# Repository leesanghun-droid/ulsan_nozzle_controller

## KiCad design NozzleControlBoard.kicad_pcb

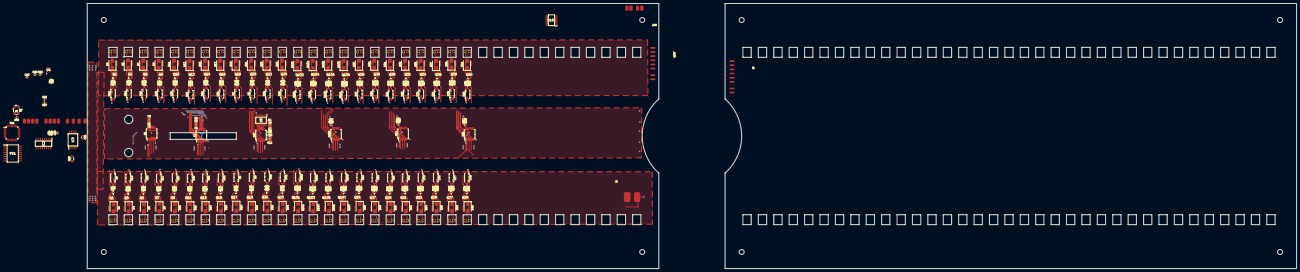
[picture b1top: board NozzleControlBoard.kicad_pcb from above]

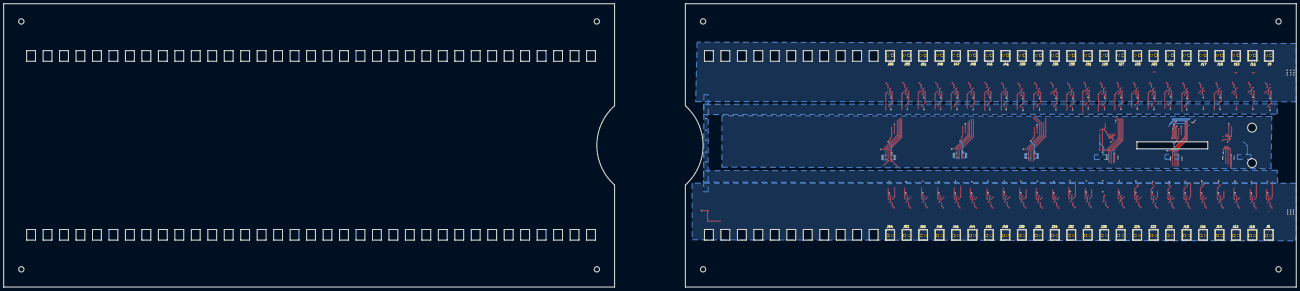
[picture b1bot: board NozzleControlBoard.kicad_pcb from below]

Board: 4 copper layers, 345.0 x 160.0 mm, 391 parts (48 on the bottom side), 276 nets.

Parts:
C1, C4, C7, C10, C16, C21, C24, C65: 0.1uF; C_0603_1608Metric
C2, C5, C8, C11, C17, C22, C25, C41, C66: 1uF; C_0603_1608Metric
C3, C6, C9, C12, C19, C23, C26, C51, C67: 10uF; C_0603_1608Metric
C18: 100uF; C_1206_3216Metric
C20, C46: NC; C_0603_1608Metric
C55: NC; C_0805_2012Metric
C63, C64: 10pF; C_0603_1608Metric
D1, D3, D4, D5, D6, D7, D8, D9, D10, D11, D12, D13, D14, D15, D16, D17, D18, D19, D20, D21, D22, D23, D24, D25, D26, D27, D28, D29, D30, D31, D32, D33, D34, D35, D36, D37, D38, D39, D40, D41, D101, D102, D103, D104, D105, D106, D107, D108: DIODE; D_SMB
IC2: MAX3094EESE+; SOIC127P600X175-16N
IC3: MAX22245BAWA+; SOIC127P1031X265-8N
J1: 24V_OUT; 24V_PAD
J2, J103: SHIFT_DATA_TOSS
J3: Conn_01x12_Male; input_pad
J8: SOL1; 2PIN
J9: SOL2; 2PIN
J10: SOL3; 2PIN
J11: SOL4; 2PIN
J12: SOL5; 2PIN
J13: SOL6; 2PIN
J14: SOL7; 2PIN
J15: SOL8; 2PIN
J16: SOL9; 2PIN
J17: SOL10; 2PIN
J18: SOL11; 2PIN
J19: SOL12; 2PIN
J20: SOL13; 2PIN
J21: SOL14; 2PIN
J22: SOL15; 2PIN
J23: SOL16; 2PIN
J24: SOL17; 2PIN
J25: SOL18; 2PIN
J26: SOL19; 2PIN
J27: SOL20; 2PIN
J28: SOL21; 2PIN
J29: SOL22; 2PIN
J30: SOL23; 2PIN
J31: SOL24; 2PIN
J32: SOL25; 2PIN
J33: SOL26; 2PIN
J34: SOL27; 2PIN
J35: SOL28; 2PIN
J36: SOL29; 2PIN
J37: SOL30; 2PIN
J38: SOL31; 2PIN
J39: SOL32; 2PIN
J40: SOL33; 2PIN
J41: SOL34; 2PIN
J42: SOL35; 2PIN
J43: SOL36; 2PIN
J44: SOL37; 2PIN
J45: SOL38; 2PIN
J46: SOL39; 2PIN
J47: SOL40; 2PIN
J48: SOL41; 2PIN
J49: SOL42; 2PIN
J50: SOL43; 2PIN
J51: SOL44; 2PIN
J52: SOL45; 2PIN
J53: SOL46; 2PIN
J54: SOL47; 2PIN
J55: SOL48; 2PIN
PS1: R05CTE05S-R; SOIC127P1030X265-16N
Q1, Q2, Q3, Q4, Q5, Q6, Q7, Q8, Q9, Q10, Q11, Q12, Q13, Q14, Q15, Q16, Q17, Q18, Q19, Q20, Q21, Q22, Q23, Q24, Q25, Q26, Q27, Q28, Q29, Q30, Q31, Q32, Q33, Q34, Q35, Q36, Q37, Q38, Q39, Q40, Q101, Q102, Q103, Q104, Q105, Q106, Q107, Q108: TPN22006NH,LQ; TPN22006NHLQ
R1: 100Ω; R_0603_1608Metric
R2, R3, R4, R5, R6, R7, R8, R9, R21, R22, R23, R24, R26, R27, R28, R29, R54, R56, R57, R58, R59, R61, R62, R63, R106, R107, R108, R109, R110, R111, R112, R113, R138, R139, R140, R141, R142, R143, R144, R145, R170, R171, R172, R173, R174, R175, R176, R177: 3.3kΩ; R_0603_1608Metric
R10, R11, R12, R13, R14, R15, R16, R17, R18, R19, R20, R25, R30, R31, R32, R33, R34, R35, R36, R37, R38, R39, R40, R41, R42, R43, R47, R48, R49, R50, R51, R64, R65, R66, R67, R68, R69, R70, R71, R72, R73, R74, R75, R76, R77, R78, R79, R96, R114, R115, R116, R117, R118, R119, R120, R121, R122, R123, R124, R125, R126, R127, R128, R129, R146, R147, R148, R149, R150, R151, R152, R153, R154, R155, R156, R157, R158, R159, R160, R161, R178, R179, R180, R181, R182, R183, R184, R185, R186, R187, R188, R189, R190, R191, R192, R193: 22kΩ; R_0603_1608Metric
R52: 5kΩ; R_0603_1608Metric
R55: 2kΩ; R_0603_1608Metric
R60: NC; R_0603_1608Metric
U1, U2, U47, U64, U81, U102: 74HCT595; SSOP-16_5.3x6.2mm_P0.65mm
U3, U6, U7, U8, U9, U12, U13, U14, U15, U16, U17, U18, U27, U28, U29, U30, U31, U32, U33, U34, U43, U44, U45, U46, U56, U57, U58, U59, U60, U61, U62, U63, U73, U74, U75, U76, U77, U78, U79, U80, U103, U104, U105, U106, U107, U108, U109, U110: TLP291; SOIC-4_4.55x2.6mm_P1.27mm
U4: ISP; TPN22006NHLQ
U5, U101: 74HC244; SOP65P640X110-20N
U11: ATmega8A-A; TQFP-32_7x7mm_P0.8mm
U87: SOL14; sol_pad
Y1: Crystal_GND24; Crystal_SMD_Abracon_ABM3B-4Pin_5.0x3.2mm

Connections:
/3.3V_3: IC2.4 (ENAC), IC2.12 (ENBD), IC2.16 (VCC), IC3.1 (VDDA)
/5V_3: C18.2, C20.2, C41.2, C46.2, C51.1, C55.1, J2.8, J3.1, J103.8, PS1.3 (+VIN_1), PS1.4 (+VIN_2)
/5V_4: C1.2, C2.2, C3.1, C4.2, C5.2, C6.1, C7.2, C8.2, C9.1, C10.2, C11.2, C12.1, C16.2, C17.2, C19.1, C21.2, C22.2, C23.1, C24.2, C25.2, C26.1, C65.2, C66.2, C67.1, IC3.8 (VDDB), J2.5, J103.5, PS1.13 (+VOUT_1), PS1.14 (+VOUT_2), R52.2, R55.1, R60.1, U1.10 (~SRCLR), U1.16 (VCC), U2.10 (~SRCLR), U2.16 (VCC), U3.1, U5.20 (VCC), U6.1, U7.1, U8.1, U9.1, U11.4 (VCC), U11.6 (VCC), U12.1, U13.1, U14.1, U15.1, U16.1, U17.1, U18.1, U27.1, U28.1, U29.1, U30.1, U31.1, U32.1, U33.1, U34.1, U43.1, U44.1, U45.1, U46.1, U47.10 (~SRCLR), U47.16 (VCC), U56.1, U57.1, U58.1, U59.1, U60.1, U61.1, U62.1, U63.1, U64.10 (~SRCLR), U64.16 (VCC), U73.1, U74.1, U75.1, U76.1, U77.1, U78.1, U79.1, U80.1, U81.10 (~SRCLR), U81.16 (VCC), U101.20 (VCC), U102.10 (~SRCLR), U102.16 (VCC), U103.1, U104.1, U105.1, U106.1, U107.1, U108.1, U109.1, U110.1
/24V2: J1.2, J3.9, J3.10, J3.11, J3.12, J8.1, J9.1, J10.1, J11.1, J12.1, J13.1, J14.1, J15.1, J16.1, J17.1, J18.1, J19.1, J20.1, J21.1, J22.1, J23.1, J24.1, J25.1, J26.1, J27.1, J28.1, J29.1, J30.1, J31.1, J32.1, J33.1, J34.1, J35.1, J36.1, J37.1, J38.1, J39.1, J40.1, J41.1, J42.1, J43.1, J44.1, J45.1, J46.1, J47.1, J48.1, J49.1, J50.1, J51.1, J52.1, J53.1, J54.1, J55.1, U3.4, U6.4, U7.4, U8.4, U9.4, U12.4, U13.4, U14.4, U15.4, U16.4, U17.4, U18.4, U27.4, U28.4, U29.4, U30.4, U31.4, U32.4, U33.4, U34.4, U43.4, U44.4, U45.4, U46.4, U56.4, U57.4, U58.4, U59.4, U60.4, U61.4, U62.4, U63.4, U73.4, U74.4, U75.4, U76.4, U77.4, U78.4, U79.4, U80.4, U87.1 (SOL+), U103.4, U104.4, U105.4, U106.4, U107.4, U108.4, U109.4, U110.4
/24V2_GND: D1.1 (K), D3.1 (K), D4.1 (K), D5.1 (K), D6.1 (K), D7.1 (K), D8.1 (K), D9.1 (K), D10.1 (K), D11.1 (K), D12.1 (K), D13.1 (K), D14.1 (K), D15.1 (K), D16.1 (K), D17.1 (K), D18.1 (K), D19.1 (K), D20.1 (K), D21.1 (K), D22.1 (K), D23.1 (K), D24.1 (K), D25.1 (K), D26.1 (K), D27.1 (K), D28.1 (K), D29.1 (K), D30.1 (K), D31.1 (K), D32.1 (K), D33.1 (K), D34.1 (K), D35.1 (K), D36.1 (K), D37.1 (K), D38.1 (K), D39.1 (K), D40.1 (K), D41.1 (K), D101.1 (K), D102.1 (K), D103.1 (K), D104.1 (K), D105.1 (K), D106.1 (K), D107.1 (K), D108.1 (K), J1.1, J3.5, J3.6, J3.7, J3.8, Q1.1 (S_1), Q1.2 (S_2), Q1.3 (S_3), Q2.1 (S_1), Q2.2 (S_2), Q2.3 (S_3), Q3.1 (S_1), Q3.2 (S_2), Q3.3 (S_3), Q4.1 (S_1), Q4.2 (S_2), Q4.3 (S_3), Q5.1 (S_1), Q5.2 (S_2), Q5.3 (S_3), Q6.1 (S_1), Q6.2 (S_2), Q6.3 (S_3), Q7.1 (S_1), Q7.2 (S_2), Q7.3 (S_3), Q8.1 (S_1), Q8.2 (S_2), Q8.3 (S_3), Q9.1 (S_1), Q9.2 (S_2), Q9.3 (S_3), Q10.1 (S_1), Q10.2 (S_2), Q10.3 (S_3), Q11.1 (S_1), Q11.2 (S_2), Q11.3 (S_3), Q12.1 (S_1), Q12.2 (S_2), Q12.3 (S_3), Q13.1 (S_1), Q13.2 (S_2), Q13.3 (S_3), Q14.1 (S_1), Q14.2 (S_2), Q14.3 (S_3), Q15.1 (S_1), Q15.2 (S_2), Q15.3 (S_3), Q16.1 (S_1), Q16.2 (S_2), Q16.3 (S_3), Q17.1 (S_1), Q17.2 (S_2), Q17.3 (S_3), Q18.1 (S_1), Q18.2 (S_2), Q18.3 (S_3), Q19.1 (S_1), Q19.2 (S_2), Q19.3 (S_3), Q20.1 (S_1), Q20.2 (S_2), Q20.3 (S_3), Q21.1 (S_1), Q21.2 (S_2), Q21.3 (S_3), Q22.1 (S_1), Q22.2 (S_2), Q22.3 (S_3), Q23.1 (S_1), Q23.2 (S_2), Q23.3 (S_3), Q24.1 (S_1), Q24.2 (S_2), Q24.3 (S_3), Q25.1 (S_1), Q25.2 (S_2), Q25.3 (S_3), Q26.1 (S_1), Q26.2 (S_2), Q26.3 (S_3), Q27.1 (S_1), Q27.2 (S_2), Q27.3 (S_3), Q28.1 (S_1), Q28.2 (S_2), Q28.3 (S_3), Q29.1 (S_1), Q29.2 (S_2), Q29.3 (S_3), Q30.1 (S_1), Q30.2 (S_2), Q30.3 (S_3), Q31.1 (S_1), Q31.2 (S_2), Q31.3 (S_3), Q32.1 (S_1), Q32.2 (S_2), Q32.3 (S_3), Q33.1 (S_1), Q33.2 (S_2), Q33.3 (S_3), Q34.1 (S_1), Q34.2 (S_2), Q34.3 (S_3), Q35.1 (S_1), Q35.2 (S_2), Q35.3 (S_3), Q36.1 (S_1), Q36.2 (S_2), Q36.3 (S_3), Q37.1 (S_1), Q37.2 (S_2), Q37.3 (S_3), Q38.1 (S_1), Q38.2 (S_2), Q38.3 (S_3), Q39.1 (S_1), Q39.2 (S_2), Q39.3 (S_3), Q40.1 (S_1), Q40.2 (S_2), Q40.3 (S_3), Q101.1 (S_1), Q101.2 (S_2), Q101.3 (S_3), Q102.1 (S_1), Q102.2 (S_2), Q102.3 (S_3), Q103.1 (S_1), Q103.2 (S_2), Q103.3 (S_3), Q104.1 (S_1), Q104.2 (S_2), Q104.3 (S_3), Q105.1 (S_1), Q105.2 (S_2), Q105.3 (S_3), Q106.1 (S_1), Q106.2 (S_2), Q106.3 (S_3), Q107.1 (S_1), Q107.2 (S_2), Q107.3 (S_3), Q108.1 (S_1), Q108.2 (S_2), Q108.3 (S_3), R11.2, R13.2, R15.2, R17.2, R19.2, R25.2, R31.2, R34.2, R36.2, R38.2, R40.2, R43.2, R47.2, R49.2, R51.2, R65.2, R67.2, R69.2, R71.2, R73.2, R75.2, R77.2, R79.2, R96.2, R115.2, R117.2, R119.2, R121.2, R123.2, R125.2, R127.2, R129.2, R147.2, R149.2, R151.2, R153.2, R155.2, R157.2, R159.2, R161.2, R179.2, R181.2, R183.2, R185.2, R187.2, R189.2, R191.2, R193.2
/CLK: J2.4, U1.11 (SRCLK), U2.11 (SRCLK), U11.26 (PC3)
/CLK_2: U5.18 (1Y0), U47.11 (SRCLK)
/CLK_3: J103.4, U64.11 (SRCLK), U81.11 (SRCLK), U101.18 (1Y0), U102.11 (SRCLK)
/DATA1_OUT: U1.9 (QH'), U2.14 (SER)
/DATA2_OUT: J2.1, U2.9 (QH')
/DATA3: IC2.3 (YA), IC3.2 (IN1)
/DATA3+: IC2.2 (A+), J3.3
/DATA3-: IC2.1 (A-), J3.2
/DATA3_INPUT: U5.12 (1Y3), U47.14 (SER)
/DATA4: IC3.7 (OUT1), R60.2, U11.30 (PD0)
/DATA4_INPUT: U101.12 (1Y3), U102.14 (SER)
/DATA4_OUT: U64.14 (SER), U102.9 (QH')
/DATA5_OUT: U64.9 (QH'), U81.14 (SER)
/DATA6_OUT: J103.1, U81.9 (QH')
/DATA_IN: U1.14 (SER), U11.23 (PC0)
/ENABLE: J2.2, R55.2, U1.13 (~OE), U2.13 (~OE), U11.24 (PC1)
/ENABLE_2: U5.14 (1Y2), U47.13 (~OE)
/ENABLE_3: J103.2, U64.13 (~OE), U81.13 (~OE), U101.14 (1Y2), U102.13 (~OE)
/GND_3: C18.1, C20.1, C41.1, C46.1, C51.2, C55.2, IC2.8 (GND), IC3.4 (GNDA), J2.7, J3.4, J103.7, PS1.1 (-VIN_1), PS1.2 (-VIN_2), PS1.5 (SGNDIN_1), PS1.6 (SGNDIN_2), PS1.7 (SGNDIN_3), PS1.8 (SGNDIN_4)
/GND_4: C1.1, C2.1, C3.2, C4.1, C5.1, C6.2, C7.1, C8.1, C9.2, C10.1, C11.1, C12.2, C16.1, C17.1, C19.2, C21.1, C22.1, C23.2, C24.1, C25.1, C26.2, C63.2, C64.2, C65.1, C66.1, C67.2, IC3.5 (GNDB), J2.6, J103.6, PS1.9 (SGNDOUT_1), PS1.11 (SGNDOUT_2), PS1.12 (SGNDOUT_3), PS1.15 (-VOUT_1), PS1.16 (-VOUT_2), R1.1, U1.8 (GND), U2.8 (GND), U5.10 (GND), U11.3 (GND), U11.5 (GND), U11.32 (PD2), U47.8 (GND), U64.8 (GND), U81.8 (GND), U101.10 (GND), U102.8 (GND), Y1.2, Y1.4
/LATCH: J2.3, U1.12 (RCLK), U2.12 (RCLK), U11.25 (PC2)
/LATCH_2: U5.16 (1Y1), U47.12 (RCLK)
/LATCH_3: J103.3, U64.12 (RCLK), U81.12 (RCLK), U101.16 (1Y1), U102.12 (RCLK)
/MISO: U4.3 (MISO), U11.16 (PB4)
/MOSI: U4.4 (MOSI), U11.15 (PB3)
/RESET: R52.1, U4.2 (RESET), U11.29 (PC6/~RESET)
/S1: R27.2, U1.15 (QA)
/S2: R21.2, U1.1 (QB)
/S3: R22.2, U1.2 (QC)
/S4: R23.2, U1.3 (QD)
/S5: R24.2, U1.4 (QE)
/S6: R26.2, U1.5 (QF)
/S7: R28.2, U1.6 (QG)
/S8: R29.2, U1.7 (QH)
/S9: R54.2, U2.15 (QA)
/S10: R56.2, U2.1 (QB)
/S11: R57.2, U2.2 (QC)
/S12: R58.2, U2.3 (QD)
/S13: R59.2, U2.4 (QE)
/S14: R61.2, U2.5 (QF)
/S15: R62.2, U2.6 (QG)
/S16: R63.2, U2.7 (QH)
/S17: R2.2, U47.15 (QA)
/S18: R3.2, U47.1 (QB)
/S19: R4.2, U47.2 (QC)
/S20: R5.2, U47.3 (QD)
/S21: R6.2, U47.4 (QE)
/S22: R7.2, U47.5 (QF)
/S23: R8.2, U47.6 (QG)
/S24: R9.2, U47.7 (QH)
/S25: R106.2, U102.15 (QA)
/S26: R107.2, U102.1 (QB)
/S27: R108.2, U102.2 (QC)
/S28: R109.2, U102.3 (QD)
/S29: R110.2, U102.4 (QE)
/S30: R111.2, U102.5 (QF)
/S31: R112.2, U102.6 (QG)
/S32: R113.2, U102.7 (QH)
/S33: R138.2, U64.15 (QA)
/S34: R139.2, U64.1 (QB)
/S35: R140.2, U64.2 (QC)
/S36: R141.2, U64.3 (QD)
/S37: R142.2, U64.4 (QE)
/S38: R143.2, U64.5 (QF)
/S39: R144.2, U64.6 (QG)
/S40: R145.2, U64.7 (QH)
/S41: R170.2, U81.15 (QA)
/S42: R171.2, U81.1 (QB)
/S43: R172.2, U81.2 (QC)
/S44: R173.2, U81.3 (QD)
/S45: R174.2, U81.4 (QE)
/S46: R175.2, U81.5 (QF)
/S47: R176.2, U81.6 (QG)
/S48: R177.2, U81.7 (QH)
/SCK: U4.1 (SCK), U11.17 (PB5)
/SOL1-: D1.2 (A), J8.2, Q1.5 (D_1), Q1.6 (D_2), Q1.7 (D_3), Q1.8 (D_4), Q1.9 (D_5)
/SOL2-: D3.2 (A), J9.2, Q2.5 (D_1), Q2.6 (D_2), Q2.7 (D_3), Q2.8 (D_4), Q2.9 (D_5)
/SOL3-: D4.2 (A), J10.2, Q3.5 (D_1), Q3.6 (D_2), Q3.7 (D_3), Q3.8 (D_4), Q3.9 (D_5)
/SOL4-: D5.2 (A), J11.2, Q4.5 (D_1), Q4.6 (D_2), Q4.7 (D_3), Q4.8 (D_4), Q4.9 (D_5)
/SOL5-: D6.2 (A), J12.2, Q5.5 (D_1), Q5.6 (D_2), Q5.7 (D_3), Q5.8 (D_4), Q5.9 (D_5)
/SOL6-: D7.2 (A), J13.2, Q6.5 (D_1), Q6.6 (D_2), Q6.7 (D_3), Q6.8 (D_4), Q6.9 (D_5)
/SOL7-: D8.2 (A), J14.2, Q7.5 (D_1), Q7.6 (D_2), Q7.7 (D_3), Q7.8 (D_4), Q7.9 (D_5)
/SOL8-: D9.2 (A), J15.2, Q8.5 (D_1), Q8.6 (D_2), Q8.7 (D_3), Q8.8 (D_4), Q8.9 (D_5)
/SOL9-: D10.2 (A), J16.2, Q9.5 (D_1), Q9.6 (D_2), Q9.7 (D_3), Q9.8 (D_4), Q9.9 (D_5)
/SOL10-: D11.2 (A), J17.2, Q10.5 (D_1), Q10.6 (D_2), Q10.7 (D_3), Q10.8 (D_4), Q10.9 (D_5)
/SOL11-: D12.2 (A), J18.2, Q11.5 (D_1), Q11.6 (D_2), Q11.7 (D_3), Q11.8 (D_4), Q11.9 (D_5)
/SOL12-: D13.2 (A), J19.2, Q12.5 (D_1), Q12.6 (D_2), Q12.7 (D_3), Q12.8 (D_4), Q12.9 (D_5)
/SOL13-: D14.2 (A), J20.2, Q13.5 (D_1), Q13.6 (D_2), Q13.7 (D_3), Q13.8 (D_4), Q13.9 (D_5)
/SOL14-: D15.2 (A), J21.2, Q14.5 (D_1), Q14.6 (D_2), Q14.7 (D_3), Q14.8 (D_4), Q14.9 (D_5)
/SOL15-: D16.2 (A), J22.2, Q15.5 (D_1), Q15.6 (D_2), Q15.7 (D_3), Q15.8 (D_4), Q15.9 (D_5)
/SOL16-: D17.2 (A), J23.2, Q16.5 (D_1), Q16.6 (D_2), Q16.7 (D_3), Q16.8 (D_4), Q16.9 (D_5)
/SOL17-: D18.2 (A), J24.2, Q17.5 (D_1), Q17.6 (D_2), Q17.7 (D_3), Q17.8 (D_4), Q17.9 (D_5)
/SOL18-: D19.2 (A), J25.2, Q18.5 (D_1), Q18.6 (D_2), Q18.7 (D_3), Q18.8 (D_4), Q18.9 (D_5)
/SOL19-: D20.2 (A), J26.2, Q19.5 (D_1), Q19.6 (D_2), Q19.7 (D_3), Q19.8 (D_4), Q19.9 (D_5)
/SOL20-: D21.2 (A), J27.2, Q20.5 (D_1), Q20.6 (D_2), Q20.7 (D_3), Q20.8 (D_4), Q20.9 (D_5)
/SOL21-: D22.2 (A), J28.2, Q21.5 (D_1), Q21.6 (D_2), Q21.7 (D_3), Q21.8 (D_4), Q21.9 (D_5)
/SOL22-: D23.2 (A), J29.2, Q22.5 (D_1), Q22.6 (D_2), Q22.7 (D_3), Q22.8 (D_4), Q22.9 (D_5)
/SOL23-: D24.2 (A), J30.2, Q23.5 (D_1), Q23.6 (D_2), Q23.7 (D_3), Q23.8 (D_4), Q23.9 (D_5)
/SOL24-: D25.2 (A), J31.2, Q24.5 (D_1), Q24.6 (D_2), Q24.7 (D_3), Q24.8 (D_4), Q24.9 (D_5)
/SOL25-: D101.2 (A), J32.2, Q101.5 (D_1), Q101.6 (D_2), Q101.7 (D_3), Q101.8 (D_4), Q101.9 (D_5)
/SOL26-: D102.2 (A), J33.2, Q102.5 (D_1), Q102.6 (D_2), Q102.7 (D_3), Q102.8 (D_4), Q102.9 (D_5)
/SOL27-: D103.2 (A), J34.2, Q103.5 (D_1), Q103.6 (D_2), Q103.7 (D_3), Q103.8 (D_4), Q103.9 (D_5)
/SOL28-: D104.2 (A), J35.2, Q104.5 (D_1), Q104.6 (D_2), Q104.7 (D_3), Q104.8 (D_4), Q104.9 (D_5)
/SOL29-: D105.2 (A), J36.2, Q105.5 (D_1), Q105.6 (D_2), Q105.7 (D_3), Q105.8 (D_4), Q105.9 (D_5)
/SOL30-: D106.2 (A), J37.2, Q106.5 (D_1), Q106.6 (D_2), Q106.7 (D_3), Q106.8 (D_4), Q106.9 (D_5)
/SOL31-: D107.2 (A), J38.2, Q107.5 (D_1), Q107.6 (D_2), Q107.7 (D_3), Q107.8 (D_4), Q107.9 (D_5)
/SOL32-: D108.2 (A), J39.2, Q108.5 (D_1), Q108.6 (D_2), Q108.7 (D_3), Q108.8 (D_4), Q108.9 (D_5)
/SOL33-: D26.2 (A), J40.2, Q25.5 (D_1), Q25.6 (D_2), Q25.7 (D_3), Q25.8 (D_4), Q25.9 (D_5)
/SOL34-: D27.2 (A), J41.2, Q26.5 (D_1), Q26.6 (D_2), Q26.7 (D_3), Q26.8 (D_4), Q26.9 (D_5)
/SOL35-: D28.2 (A), J42.2, Q27.5 (D_1), Q27.6 (D_2), Q27.7 (D_3), Q27.8 (D_4), Q27.9 (D_5)
/SOL36-: D29.2 (A), J43.2, Q28.5 (D_1), Q28.6 (D_2), Q28.7 (D_3), Q28.8 (D_4), Q28.9 (D_5)
/SOL37-: D30.2 (A), J44.2, Q29.5 (D_1), Q29.6 (D_2), Q29.7 (D_3), Q29.8 (D_4), Q29.9 (D_5)
/SOL38-: D31.2 (A), J45.2, Q30.5 (D_1), Q30.6 (D_2), Q30.7 (D_3), Q30.8 (D_4), Q30.9 (D_5)
/SOL39-: D32.2 (A), J46.2, Q31.5 (D_1), Q31.6 (D_2), Q31.7 (D_3), Q31.8 (D_4), Q31.9 (D_5)
/SOL40-: D33.2 (A), J47.2, Q32.5 (D_1), Q32.6 (D_2), Q32.7 (D_3), Q32.8 (D_4), Q32.9 (D_5)
/SOL41-: D34.2 (A), J48.2, Q33.5 (D_1), Q33.6 (D_2), Q33.7 (D_3), Q33.8 (D_4), Q33.9 (D_5)
/SOL42-: D35.2 (A), J49.2, Q34.5 (D_1), Q34.6 (D_2), Q34.7 (D_3), Q34.8 (D_4), Q34.9 (D_5)
/SOL43-: D36.2 (A), J50.2, Q35.5 (D_1), Q35.6 (D_2), Q35.7 (D_3), Q35.8 (D_4), Q35.9 (D_5)
/SOL44-: D37.2 (A), J51.2, Q36.5 (D_1), Q36.6 (D_2), Q36.7 (D_3), Q36.8 (D_4), Q36.9 (D_5)
/SOL45-: D38.2 (A), J52.2, Q37.5 (D_1), Q37.6 (D_2), Q37.7 (D_3), Q37.8 (D_4), Q37.9 (D_5)
/SOL46-: D39.2 (A), J53.2, Q38.5 (D_1), Q38.6 (D_2), Q38.7 (D_3), Q38.8 (D_4), Q38.9 (D_5), U87.3 (SOL-), U87.4 (LED-)
/SOL47-: D40.2 (A), J54.2, Q39.5 (D_1), Q39.6 (D_2), Q39.7 (D_3), Q39.8 (D_4), Q39.9 (D_5)
/SOL48-: D41.2 (A), J55.2, Q40.5 (D_1), Q40.6 (D_2), Q40.7 (D_3), Q40.8 (D_4), Q40.9 (D_5)
/X_TAL1: C63.1, U11.7 (PB6/XTAL1), Y1.1
/X_TAL2: C64.1, U11.8 (PB7/XTAL2), Y1.3
unnamed: Q1.4 (G), R42.1, R43.1
unnamed: Q2.4 (G), R33.1, R34.1
unnamed: Q3.4 (G), R35.1, R36.1
unnamed: Q4.4 (G), R37.1, R38.1
unnamed: Q5.4 (G), R39.1, R40.1
unnamed: Q6.4 (G), R41.1, R47.1
unnamed: Q7.4 (G), R48.1, R49.1
unnamed: Q8.4 (G), R50.1, R51.1
unnamed: Q9.4 (G), R64.1, R65.1
unnamed: Q10.4 (G), R66.1, R67.1
unnamed: Q11.4 (G), R68.1, R69.1
unnamed: Q12.4 (G), R70.1, R71.1
unnamed: Q13.4 (G), R72.1, R73.1
unnamed: Q14.4 (G), R74.1, R75.1
unnamed: Q15.4 (G), R76.1, R77.1
unnamed: Q16.4 (G), R78.1, R79.1
unnamed: Q17.4 (G), R10.1, R11.1
unnamed: Q18.4 (G), R12.1, R13.1
unnamed: Q19.4 (G), R14.1, R15.1
unnamed: Q20.4 (G), R16.1, R17.1
unnamed: Q21.4 (G), R18.1, R19.1
unnamed: Q22.4 (G), R20.1, R25.1
unnamed: Q23.4 (G), R30.1, R31.1
unnamed: Q24.4 (G), R32.1, R96.1
unnamed: Q25.4 (G), R146.1, R147.1
unnamed: Q26.4 (G), R148.1, R149.1
unnamed: Q27.4 (G), R150.1, R151.1
unnamed: Q28.4 (G), R152.1, R153.1
unnamed: Q29.4 (G), R154.1, R155.1
unnamed: Q30.4 (G), R156.1, R157.1
unnamed: Q31.4 (G), R158.1, R159.1
unnamed: Q32.4 (G), R160.1, R161.1
unnamed: Q33.4 (G), R178.1, R179.1
unnamed: Q34.4 (G), R180.1, R181.1
unnamed: Q35.4 (G), R182.1, R183.1
unnamed: Q36.4 (G), R184.1, R185.1
unnamed: Q37.4 (G), R186.1, R187.1
unnamed: Q38.4 (G), R188.1, R189.1
unnamed: Q39.4 (G), R190.1, R191.1
unnamed: Q40.4 (G), R192.1, R193.1
unnamed: Q101.4 (G), R114.1, R115.1
unnamed: Q102.4 (G), R116.1, R117.1
unnamed: Q103.4 (G), R118.1, R119.1
unnamed: Q104.4 (G), R120.1, R121.1
unnamed: Q105.4 (G), R122.1, R123.1
unnamed: Q106.4 (G), R124.1, R125.1
unnamed: Q107.4 (G), R126.1, R127.1
unnamed: Q108.4 (G), R128.1, R129.1
unnamed: R2.1, U6.2
unnamed: R3.1, U7.2
unnamed: R4.1, U8.2
unnamed: R5.1, U9.2
unnamed: R6.1, U43.2
unnamed: R7.1, U44.2
unnamed: R8.1, U45.2
unnamed: R9.1, U46.2
unnamed: R10.2, U6.3
unnamed: R12.2, U7.3
unnamed: R14.2, U8.3
unnamed: R16.2, U9.3
unnamed: R18.2, U43.3
unnamed: R20.2, U44.3
unnamed: R21.1, U12.2
unnamed: R22.1, U13.2
unnamed: R23.1, U14.2
unnamed: R24.1, U15.2
unnamed: R26.1, U16.2
unnamed: R27.1, U3.2
unnamed: R28.1, U17.2
unnamed: R29.1, U18.2
unnamed: R30.2, U45.3
unnamed: R32.2, U46.3
unnamed: R33.2, U12.3
unnamed: R35.2, U13.3
unnamed: R37.2, U14.3
unnamed: R39.2, U15.3
unnamed: R41.2, U16.3
unnamed: R42.2, U3.3
unnamed: R48.2, U17.3
unnamed: R50.2, U18.3
unnamed: R54.1, U27.2
unnamed: R56.1, U28.2
unnamed: R57.1, U29.2
unnamed: R58.1, U30.2
unnamed: R59.1, U31.2
unnamed: R61.1, U32.2
unnamed: R62.1, U33.2
unnamed: R63.1, U34.2
unnamed: R64.2, U27.3
unnamed: R66.2, U28.3
unnamed: R68.2, U29.3
unnamed: R70.2, U30.3
unnamed: R72.2, U31.3
unnamed: R74.2, U32.3
unnamed: R76.2, U33.3
unnamed: R78.2, U34.3
unnamed: R106.1, U103.2
unnamed: R107.1, U104.2
unnamed: R108.1, U105.2
unnamed: R109.1, U106.2
unnamed: R110.1, U107.2
unnamed: R111.1, U108.2
unnamed: R112.1, U109.2
unnamed: R113.1, U110.2
unnamed: R114.2, U103.3
unnamed: R116.2, U104.3
unnamed: R118.2, U105.3
unnamed: R120.2, U106.3
unnamed: R122.2, U107.3
unnamed: R124.2, U108.3
unnamed: R126.2, U109.3
unnamed: R128.2, U110.3
unnamed: R138.1, U56.2
unnamed: R139.1, U57.2
unnamed: R140.1, U58.2
unnamed: R141.1, U59.2
unnamed: R142.1, U60.2
unnamed: R143.1, U61.2
unnamed: R144.1, U62.2
unnamed: R145.1, U63.2
unnamed: R146.2, U56.3
unnamed: R148.2, U57.3
unnamed: R150.2, U58.3
unnamed: R152.2, U59.3
unnamed: R154.2, U60.3
unnamed: R156.2, U61.3
unnamed: R158.2, U62.3
unnamed: R160.2, U63.3
unnamed: R170.1, U73.2
unnamed: R171.1, U74.2
unnamed: R172.1, U75.2
unnamed: R173.1, U76.2
unnamed: R174.1, U77.2
unnamed: R175.1, U78.2
unnamed: R176.1, U79.2
unnamed: R177.1, U80.2
unnamed: R178.2, U73.3
unnamed: R180.2, U74.3
unnamed: R182.2, U75.3
unnamed: R184.2, U76.3
unnamed: R186.2, U77.3
unnamed: R188.2, U78.3
unnamed: R190.2, U79.3
unnamed: R192.2, U80.3
unnamed: R1.2, U5.1 (1OE), U5.19 (2OE)
unnamed: U101.1 (1OE), U101.19 (2OE)

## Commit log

2023-03-10 .
    .
2023-03-29 ,
    ,
2023-03-31 이은혜
    텍스트를 추가함
2023-03-31 이은혜
    3/31
2023-04-01 이은혜
    4/1
2023-04-02 이은혜
    4/2
2023-04-04 이은혜
    4/3
2023-04-05 이은혜
    확인바람
2023-04-05 이은혜
    4/5
2023-04-06 이은혜
    4/7 32CH 확인해주세요
2023-04-07 이은혜
    ....
2023-04-07 이은혜
    4/7 이번주는 고만@!
2023-04-08 이은혜
    4/8
2023-04-09 이은혜
    4/9
2023-04-11 이은혜
    4/11
2023-04-12 이은혜
    4/12
2023-04-13 이은혜
    4/13
2023-04-14 이은혜
    4/14
2023-04-15 이은혜
    4/15
2023-04-17 이은혜
    4/17
2023-04-18 이은혜
    4/18
2023-04-18 이은혜
    오류수정
